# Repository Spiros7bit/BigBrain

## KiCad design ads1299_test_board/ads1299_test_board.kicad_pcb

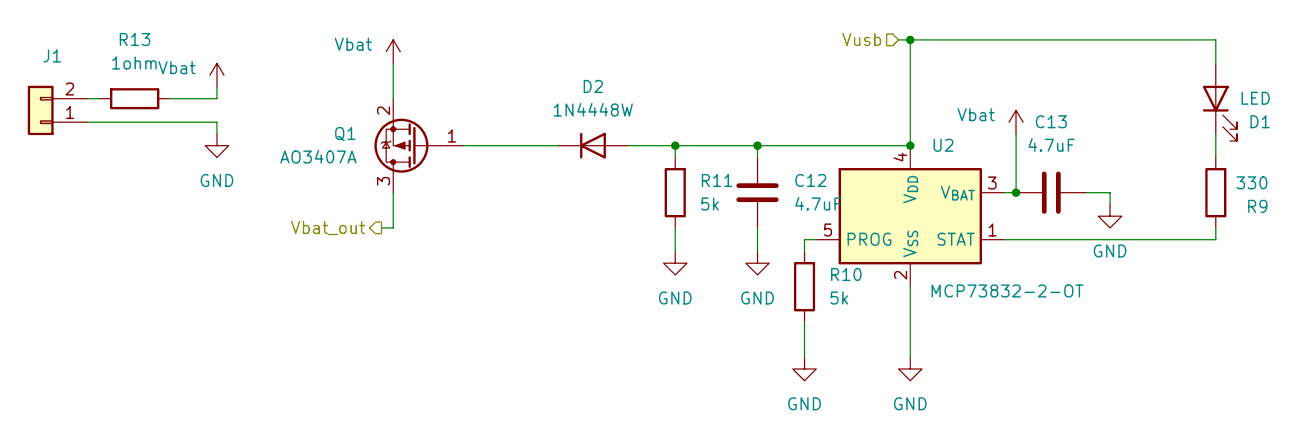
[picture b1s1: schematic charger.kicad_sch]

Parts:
C12, C13: 4.7uF; C_0402_1005Metric_Pad0.74x0.62mm_HandSolder
D1: LED; LED_0603_1608Metric
D2: 1N4448W; D_SOD-123
J1: Conn_01x02; JST_EH_B2B-EH-A_1x02_P2.50mm_Vertical
Q1: AO3407A; SOT-23
R9: 330; R_0402_1005Metric_Pad0.72x0.64mm_HandSolder
R10, R11: 5k; R_0402_1005Metric_Pad0.72x0.64mm_HandSolder
R13: 1ohm; TO-252-2_TabPin1
U2: MCP73832-2-OT; SOT-23-5

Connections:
/USB/Vbus: C12.1, D1.2 (A), D2.2 (A), Q1.3 (D), R11.2, U2.4 (V_{DD}); also elsewhere on the board
GND: C12.2, C13.2, J1.1, R10.1, R11.1, U2.2 (V_{SS}); also elsewhere on the board
unnamed: D1.1 (K), R9.2
unnamed: D2.1 (K), Q1.1 (G)
unnamed: J1.2, R13.2
unnamed: R10.2, U2.5 (PROG)
unnamed: R9.1, U2.1 (STAT)
Vbat: C13.1, Q1.2 (S), R13.1, U2.3 (V_{BAT})

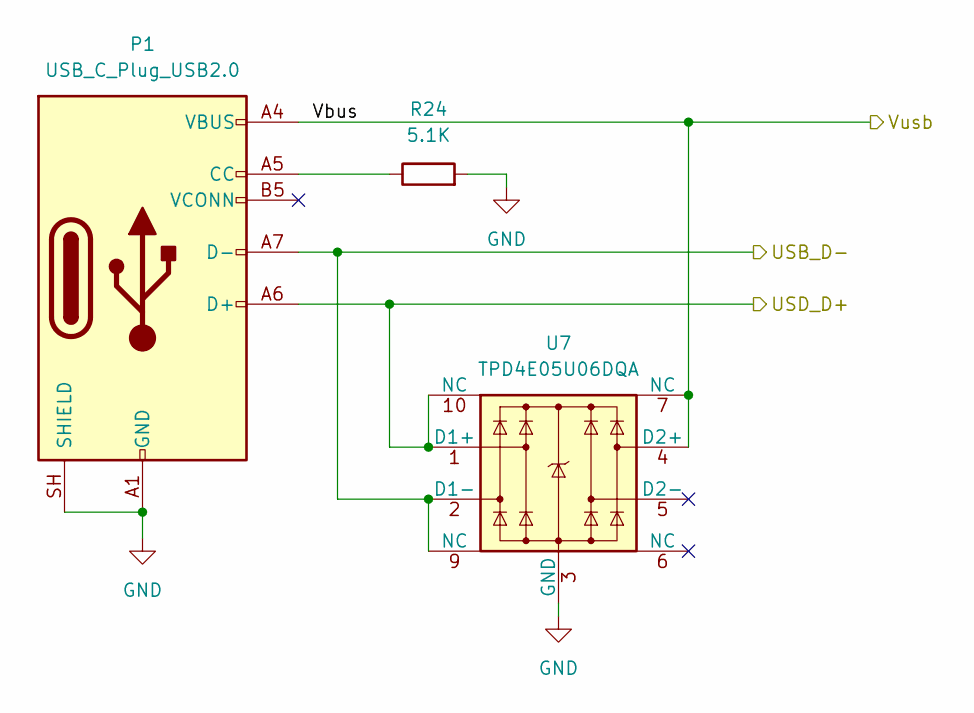
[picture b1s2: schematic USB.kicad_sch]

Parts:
P1: USB_C_Plug_USB2.0; USB_C_Receptacle_G-Switch_GT-USB-7010ASV
R24: 5.1K; C_0402_1005Metric_Pad0.74x0.62mm_HandSolder
U7: TPD4E05U06DQA; USON-10_2.5x1.0mm_P0.5mm

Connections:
/ESP32_S3_WROOM/USB_D+: P1.A6 (D+), U7.1 (D1+), U7.10 (NC); also elsewhere on the board
/ESP32_S3_WROOM/USB_D-: P1.A7 (D-), U7.2 (D1-), U7.9 (NC); also elsewhere on the board
/USB/Vbus: P1.A4 (VBUS), P1.A9 (VBUS), P1.B4 (VBUS), P1.B9 (VBUS), U7.4 (D2+), U7.7 (NC); also elsewhere on the board
GND: P1.A1 (GND), P1.A12 (GND), P1.B1 (GND), P1.B12 (GND), P1.SH (SHIELD), R24.2, U7.3 (GND), U7.8 (GND); also elsewhere on the board
unnamed: P1.A5 (CC), R24.1

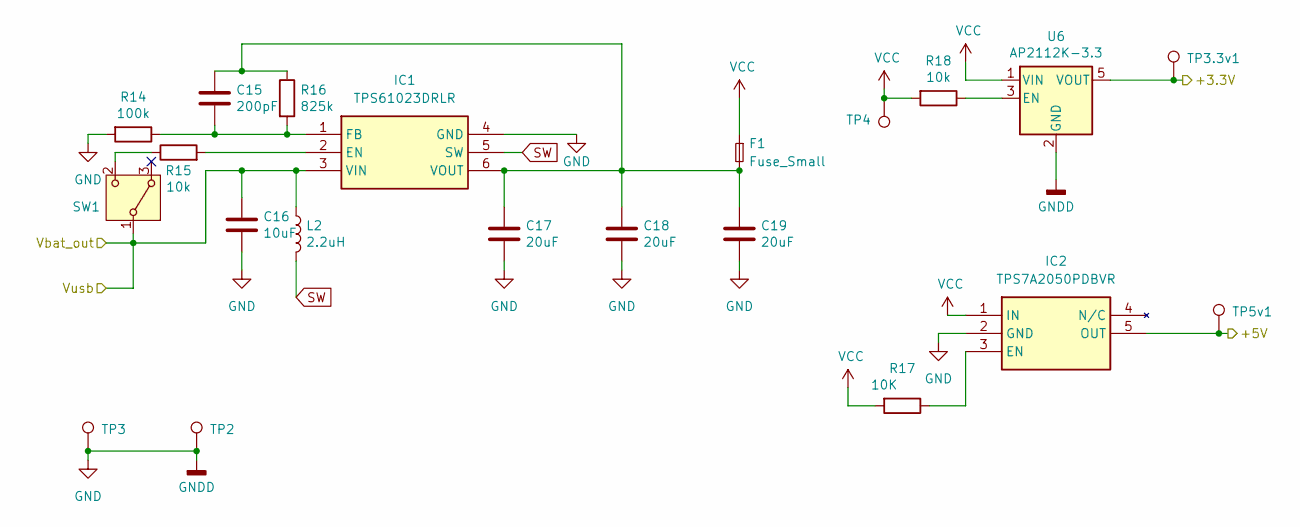
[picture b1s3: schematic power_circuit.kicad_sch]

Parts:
C15: 200pF; C_0402_1005Metric_Pad0.74x0.62mm_HandSolder
C16: 10uF; C_0402_1005Metric_Pad0.74x0.62mm_HandSolder
C17, C18, C19: 20uF; C_0805_2012Metric_Pad1.18x1.45mm_HandSolder
F1: Fuse_Small; Fuse_2512_6332Metric_Pad1.52x3.35mm_HandSolder
IC1: TPS61023DRLR; SOT-563; Manufacturer_Part_Number TPS61023DRLR; Mouser Part Number 595-TPS61023DRLR
IC2: TPS7A2050PDBVR; SOT-23-5_HandSoldering; Manufacturer_Part_Number TPS7A2050PDBVR; Mouser Part Number 595-TPS7A2050PDBVR
L2: 2.2uH; L_Wuerth_HCI-5040
R14: 100k; R_0402_1005Metric_Pad0.72x0.64mm_HandSolder
R15, R18: 10k; R_0402_1005Metric_Pad0.72x0.64mm_HandSolder
R16: 825k; R_0402_1005Metric_Pad0.72x0.64mm_HandSolder
R17: 10K; R_0402_1005Metric_Pad0.72x0.64mm_HandSolder
SW1: EG1218; SW_Slide-03_Wuerth-WS-SLTV_10x2.5x6.4_P2.54mm
TP2, TP3, TP3.3v1, TP4, TP5v1: TestPoint; TestPoint_Pad_D1.0mm
U6: AP2112K-3.3; SOT-23-5

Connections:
/USB/Vbus: C16.1, IC1.3 (VIN), L2.1, SW1.1 (B); also elsewhere on the board
/ads1299_AFE_/AVDD: IC2.5 (OUT), TP5v1.1 (1_1); also elsewhere on the board
/ads1299_AFE_/DVDD: TP3.3v1.1 (1_1), U6.5 (VOUT); also elsewhere on the board
GND: C16.2, C17.2, C18.2, C19.2, IC1.4 (GND), IC2.2 (GND), R14.2, TP2.1 (1_1), TP3.1 (1_1), U6.2 (GND); also elsewhere on the board
unnamed: IC1.2 (EN), R15.2
unnamed: C15.2, IC1.1 (FB), R14.1, R16.2
unnamed: C15.1, C17.1, C18.1, C19.1, F1.2, IC1.6 (VOUT), R16.1
unnamed: IC2.3 (EN), R17.1
unnamed: R15.1, SW1.2 (C)
unnamed: R18.1, U6.3 (EN)
SW: IC1.5 (SW), L2.2
VCC: F1.1, IC2.1 (IN), R17.2, R18.2, TP4.1 (1_1), U6.1 (VIN)

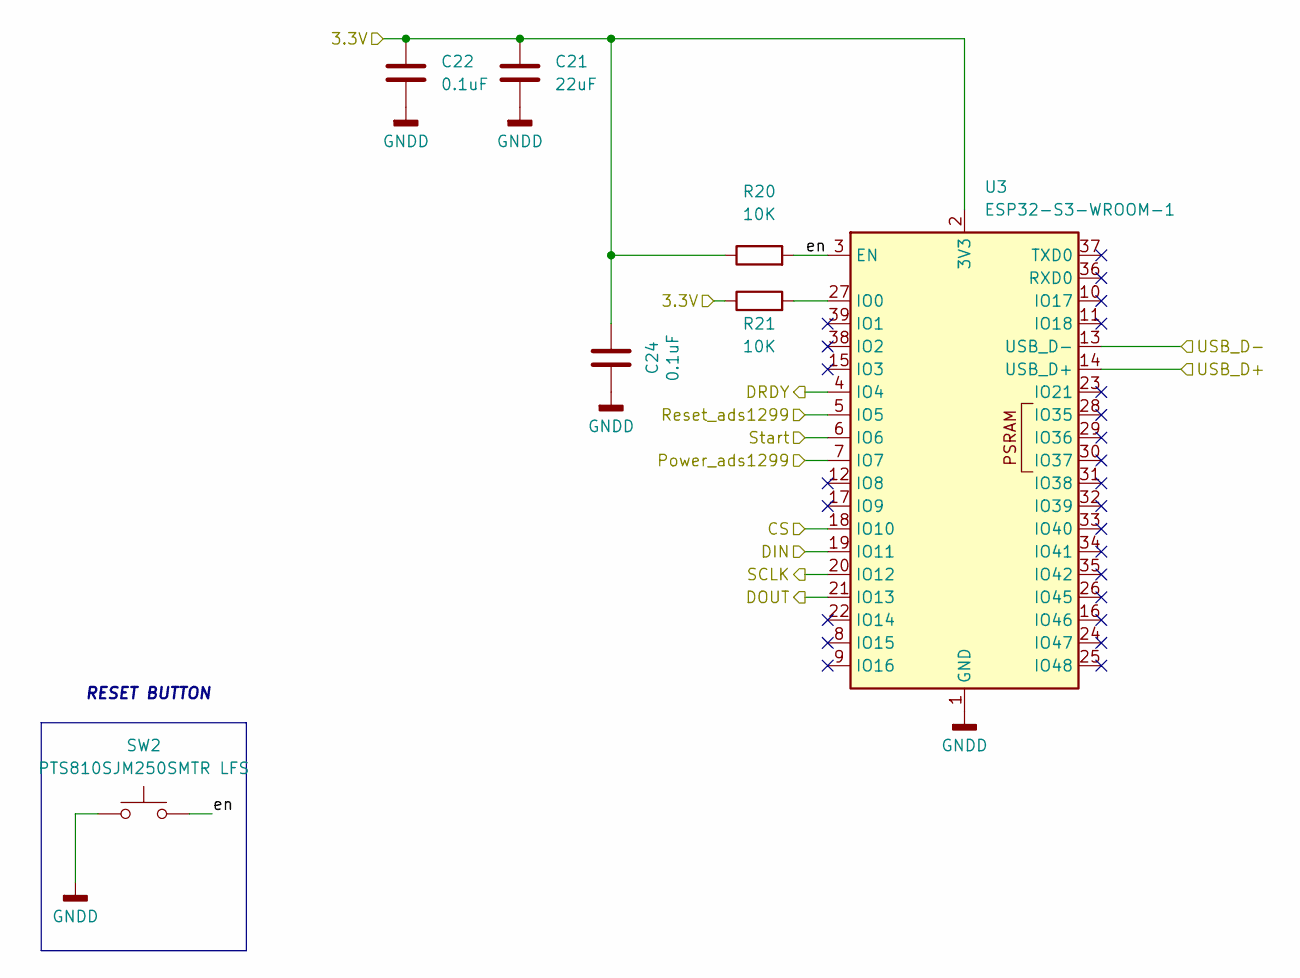
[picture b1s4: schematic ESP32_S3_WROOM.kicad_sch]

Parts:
C21: 22uF; C_0603_1608Metric_Pad1.08x0.95mm_HandSolder
C22, C24: 0.1uF; C_0402_1005Metric_Pad0.74x0.62mm_HandSolder
R20, R21: 10K; R_0402_1005Metric_Pad0.72x0.64mm_HandSolder
SW2: PTS810SJM250SMTR LFS; SW_SPST_PTS810
U3: ESP32-S3-WROOM-1

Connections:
/ESP32_S3_WROOM/CS: U3.18 (IO10); also elsewhere on the board
/ESP32_S3_WROOM/DIN: U3.19 (IO11); also elsewhere on the board
/ESP32_S3_WROOM/DOUT: U3.21 (IO13); also elsewhere on the board
/ESP32_S3_WROOM/DRDY: U3.4 (IO4); also elsewhere on the board
/ESP32_S3_WROOM/Power_ads1299: U3.7 (IO7); also elsewhere on the board
/ESP32_S3_WROOM/Reset_ads1299: U3.5 (IO5); also elsewhere on the board
/ESP32_S3_WROOM/SCLK: U3.20 (IO12); also elsewhere on the board
/ESP32_S3_WROOM/Start: U3.6 (IO6); also elsewhere on the board
/ESP32_S3_WROOM/USB_D+: U3.14 (USB_D+); also elsewhere on the board
/ESP32_S3_WROOM/USB_D-: U3.13 (USB_D-); also elsewhere on the board
/ESP32_S3_WROOM/en: R20.2, SW2.2, U3.3 (EN)
/ads1299_AFE_/DVDD: C21.1, C22.1, C24.1, R20.1, R21.1, U3.2 (3V3); also elsewhere on the board
GND: C21.2, C22.2, C24.2, SW2.1, U3.1 (GND), U3.40 (GND), U3.41 (GND); also elsewhere on the board
unnamed: R21.2, U3.27 (IO0)

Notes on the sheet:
RESET BUTTON

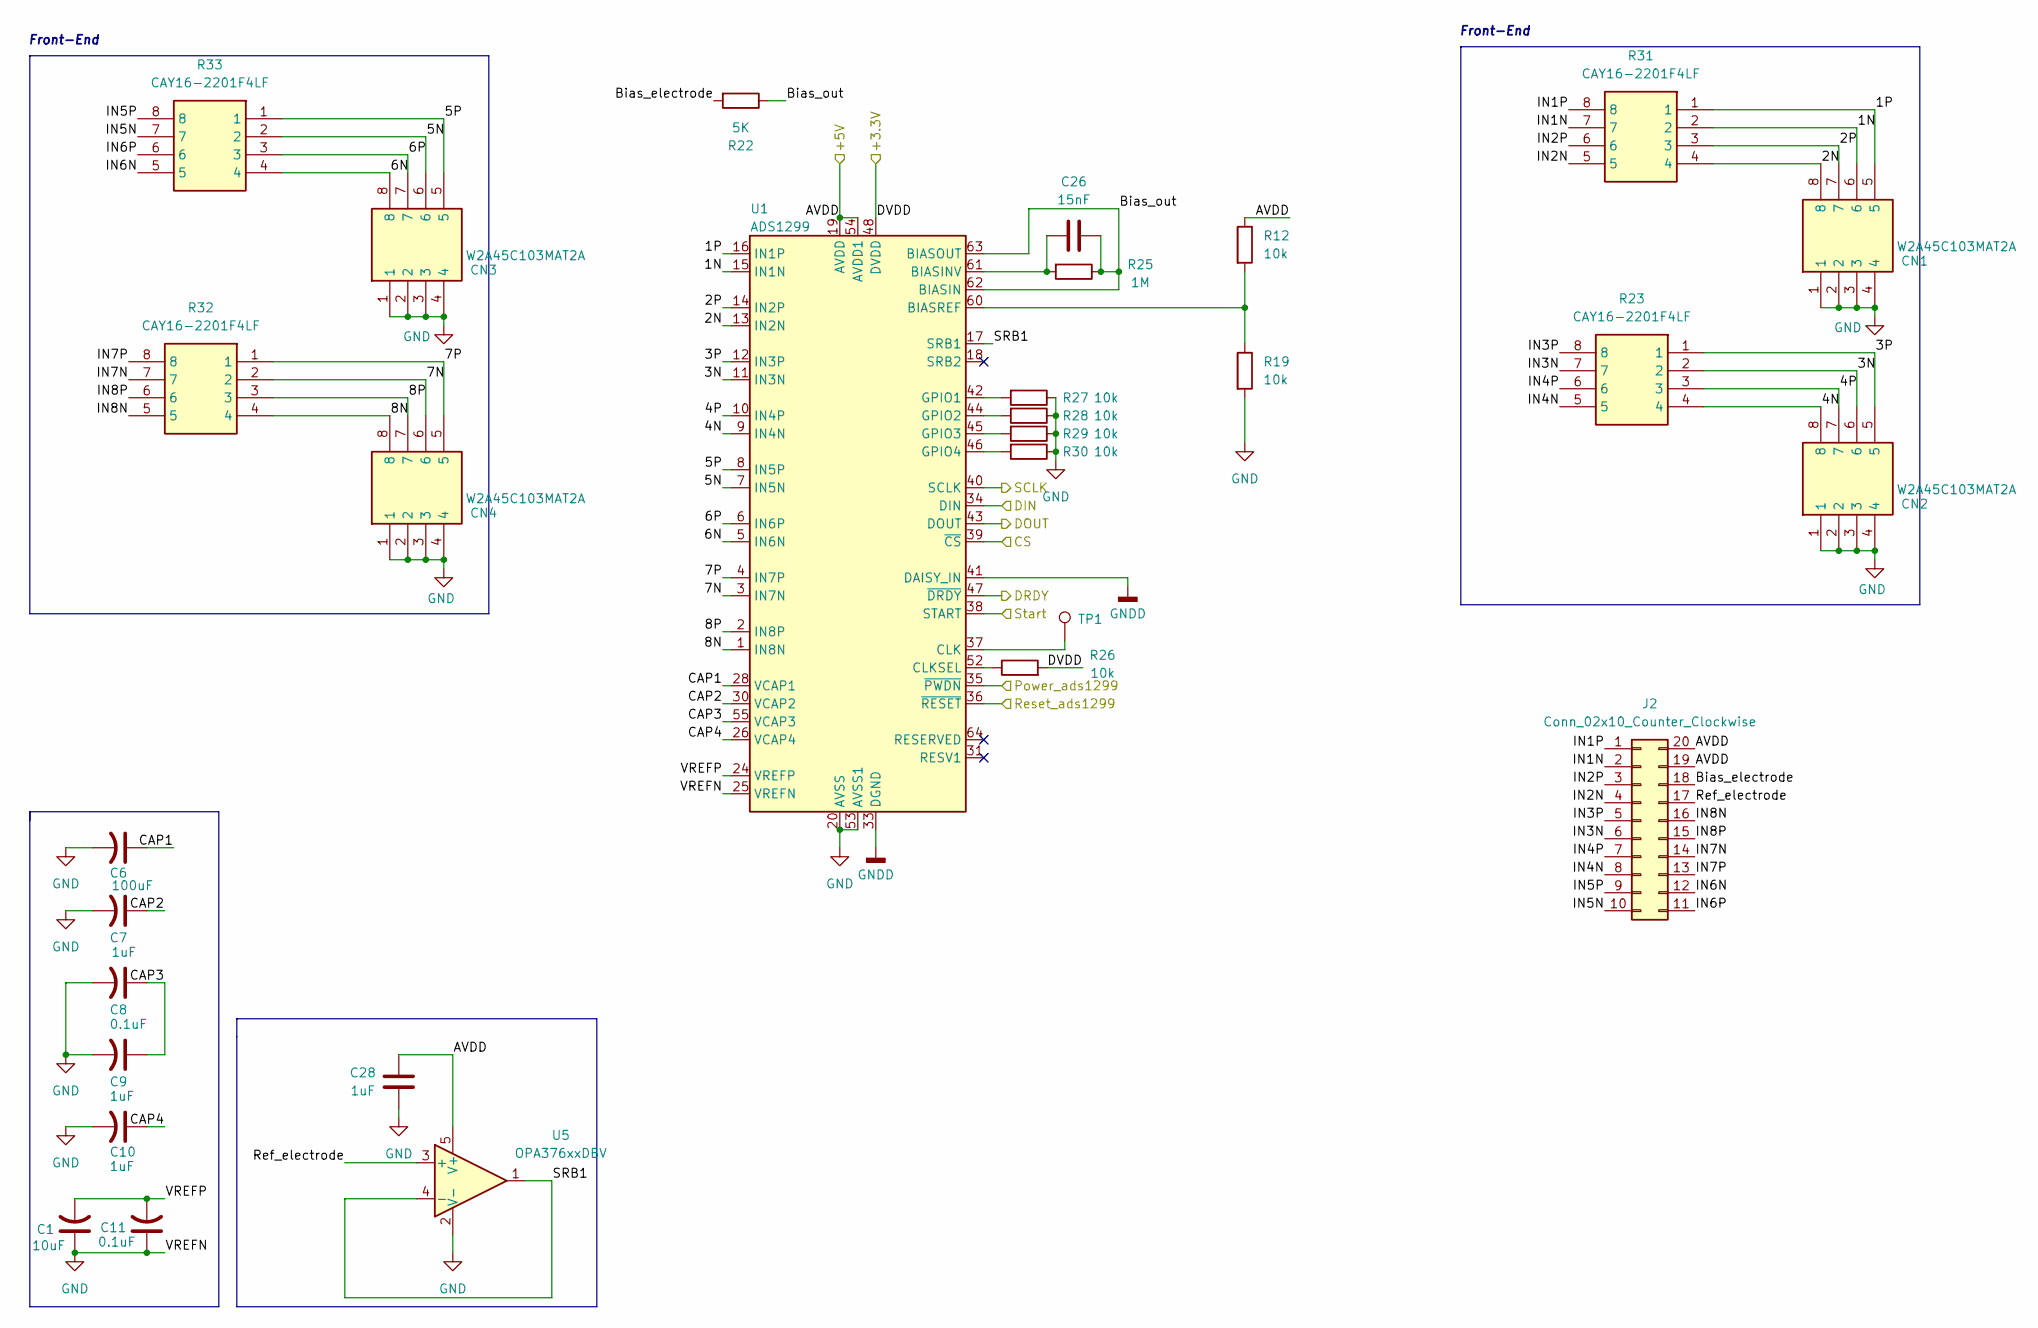
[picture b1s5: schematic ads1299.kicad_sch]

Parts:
C1: 10uF; C_0402_1005Metric_Pad0.74x0.62mm_HandSolder
C6: 100uF; C_1206_3216Metric_Pad1.33x1.80mm_HandSolder
C7, C9, C10, C28: 1uF; C_0402_1005Metric_Pad0.74x0.62mm_HandSolder
C8, C11: 0.1uF; C_0402_1005Metric_Pad0.74x0.62mm_HandSolder
C26: 15nF; C_0402_1005Metric_Pad0.74x0.62mm_HandSolder
CN1, CN2, CN3, CN4: W2A45C103MAT2A; Manufacturer_Part_Number W2A45C103MAT2A; Mouser Part Number 581-W2A45C103MAT2A
J2: Conn_02x10_Counter_Clockwise; IDC-Header_2x10_P2.54mm_Vertical
R12, R19, R26, R27, R28, R29, R30: 10k; R_0402_1005Metric_Pad0.72x0.64mm_HandSolder
R22: 5K; C_0402_1005Metric_Pad0.74x0.62mm_HandSolder
R23, R31, R32, R33: CAY16-2201F4LF; RESCAX80P160X320X60-8N; Manufacturer_Part_Number CAY16-2201F4LF; Mouser Part Number 652-CAY16-2201F4LF
R25: 1M; R_0402_1005Metric_Pad0.72x0.64mm_HandSolder
TP1: TestPoint; TestPoint_Pad_D1.0mm
U1: ADS1299; TQFP-64_10x10mm_P0.5mm
U5: OPA376xxDBV; SOT-23-5

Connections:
/ESP32_S3_WROOM/CS: U1.39 (~CS); also elsewhere on the board
/ESP32_S3_WROOM/DIN: U1.34 (DIN); also elsewhere on the board
/ESP32_S3_WROOM/DOUT: U1.43 (DOUT); also elsewhere on the board
/ESP32_S3_WROOM/DRDY: U1.47 (~DRDY); also elsewhere on the board
/ESP32_S3_WROOM/Power_ads1299: U1.35 (~PWDN); also elsewhere on the board
/ESP32_S3_WROOM/Reset_ads1299: U1.36 (~RESET); also elsewhere on the board
/ESP32_S3_WROOM/SCLK: U1.40 (SCLK); also elsewhere on the board
/ESP32_S3_WROOM/Start: U1.38 (START); also elsewhere on the board
/ads1299_AFE_/1N: CN1.6, R31.2, U1.15 (IN1N)
/ads1299_AFE_/1P: CN1.5, R31.1, U1.16 (IN1P)
/ads1299_AFE_/2N: CN1.8, R31.4, U1.13 (IN2N)
/ads1299_AFE_/2P: CN1.7, R31.3, U1.14 (IN2P)
/ads1299_AFE_/3N: CN2.6, R23.2, U1.11 (IN3N)
/ads1299_AFE_/3P: CN2.5, R23.1, U1.12 (IN3P)
/ads1299_AFE_/4N: CN2.8, R23.4, U1.9 (IN4N)
/ads1299_AFE_/4P: CN2.7, R23.3, U1.10 (IN4P)
/ads1299_AFE_/5N: CN3.6, R33.2, U1.7 (IN5N)
/ads1299_AFE_/5P: CN3.5, R33.1, U1.8 (IN5P)
/ads1299_AFE_/6N: CN3.8, R33.4, U1.5 (IN6N)
/ads1299_AFE_/6P: CN3.7, R33.3, U1.6 (IN6P)
/ads1299_AFE_/7N: CN4.6, R32.2, U1.3 (IN7N)
/ads1299_AFE_/7P: CN4.5, R32.1, U1.4 (IN7P)
/ads1299_AFE_/8N: CN4.8, R32.4, U1.1 (IN8N)
/ads1299_AFE_/8P: CN4.7, R32.3, U1.2 (IN8P)
/ads1299_AFE_/AVDD: C28.1, J2.19, J2.20, R12.1, U1.19 (AVDD), U1.21 (AVDD), U1.22 (AVDD), U1.54 (AVDD1), U1.56 (AVDD), U1.59 (AVDD), U5.5 (V+); also elsewhere on the board
/ads1299_AFE_/Bias_electrode: J2.18, R22.2
/ads1299_AFE_/Bias_out: C26.2, R22.1, R25.1, U1.62 (BIASIN), U1.63 (BIASOUT)
/ads1299_AFE_/CAP1: C6.1, U1.28 (VCAP1)
/ads1299_AFE_/CAP2: C7.1, U1.30 (VCAP2)
/ads1299_AFE_/CAP3: C8.1, C9.1, U1.55 (VCAP3)
/ads1299_AFE_/CAP4: C10.1, U1.26 (VCAP4)
/ads1299_AFE_/DVDD: R26.2, U1.48 (DVDD), U1.50 (DVDD); also elsewhere on the board
/ads1299_AFE_/IN1N: J2.2, R31.7
/ads1299_AFE_/IN1P: J2.1, R31.8
/ads1299_AFE_/IN2N: J2.4, R31.5
/ads1299_AFE_/IN2P: J2.3, R31.6
/ads1299_AFE_/IN3N: J2.6, R23.7
/ads1299_AFE_/IN3P: J2.5, R23.8
/ads1299_AFE_/IN4N: J2.8, R23.5
/ads1299_AFE_/IN4P: J2.7, R23.6
/ads1299_AFE_/IN5N: J2.10, R33.7
/ads1299_AFE_/IN5P: J2.9, R33.8
/ads1299_AFE_/IN6N: J2.12, R33.5
/ads1299_AFE_/IN6P: J2.11, R33.6
/ads1299_AFE_/IN7N: J2.14, R32.7
/ads1299_AFE_/IN7P: J2.13, R32.8
/ads1299_AFE_/IN8N: J2.16, R32.5
/ads1299_AFE_/IN8P: J2.15, R32.6
/ads1299_AFE_/Ref_electrode: J2.17, U5.3 (+)
/ads1299_AFE_/SRB1: U1.17 (SRB1), U5.1, U5.4 (-)
/ads1299_AFE_/VREFP: C1.2, C11.2, U1.24 (VREFP)
GND: C1.1, C6.2, C7.2, C8.2, C9.2, C10.2, C11.1, C28.2, CN1.1, CN1.2, CN1.3, CN1.4, CN2.1, CN2.2, CN2.3, CN2.4, CN3.1, CN3.2, CN3.3, CN3.4, CN4.1, CN4.2, CN4.3, CN4.4, R19.2, R27.1, R28.1, R29.1, R30.1, U1.20 (AVSS), U1.23 (AVSS), U1.25 (VREFN), U1.32 (AVSS), U1.33 (DGND), U1.41 (DAISY_IN), U1.49 (DGND), U1.51 (DGND), U1.53 (AVSS1), U1.57 (AVSS), U1.58 (AVSS), U5.2 (V-); also elsewhere on the board
unnamed: C26.1, R25.2, U1.61 (BIASINV)
unnamed: R12.2, R19.1, U1.60 (BIASREF)
unnamed: TP1.1 (1_1), U1.37 (CLK)
unnamed: R26.1, U1.52 (CLKSEL)
unnamed: R27.2, U1.42 (GPIO1)
unnamed: R28.2, U1.44 (GPIO2)
unnamed: R29.2, U1.45 (GPIO3)
unnamed: R30.2, U1.46 (GPIO4)

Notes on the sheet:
Front-End

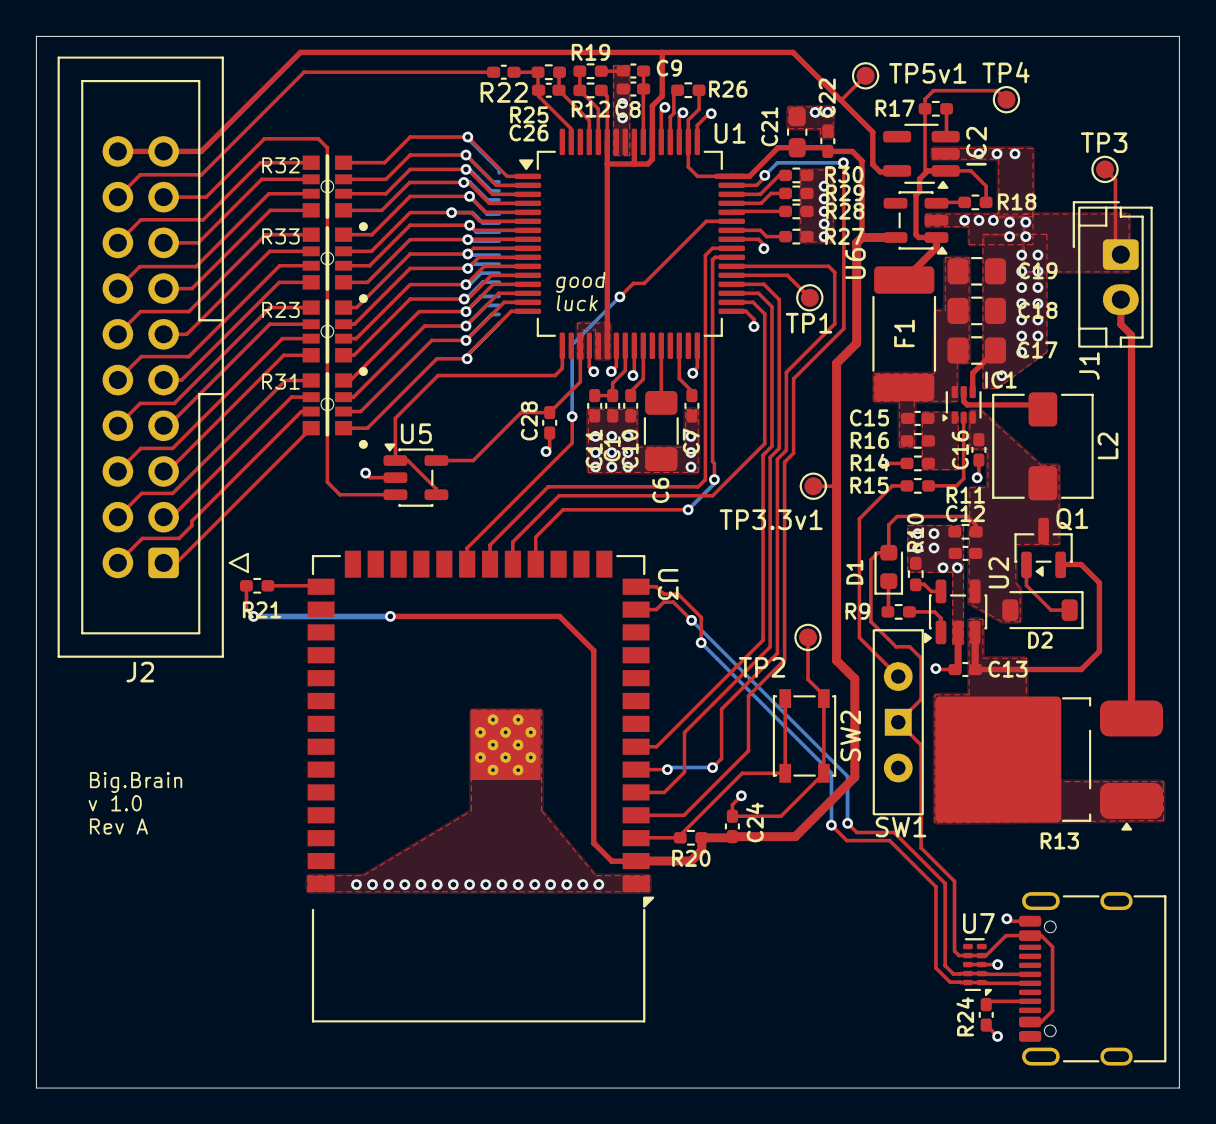
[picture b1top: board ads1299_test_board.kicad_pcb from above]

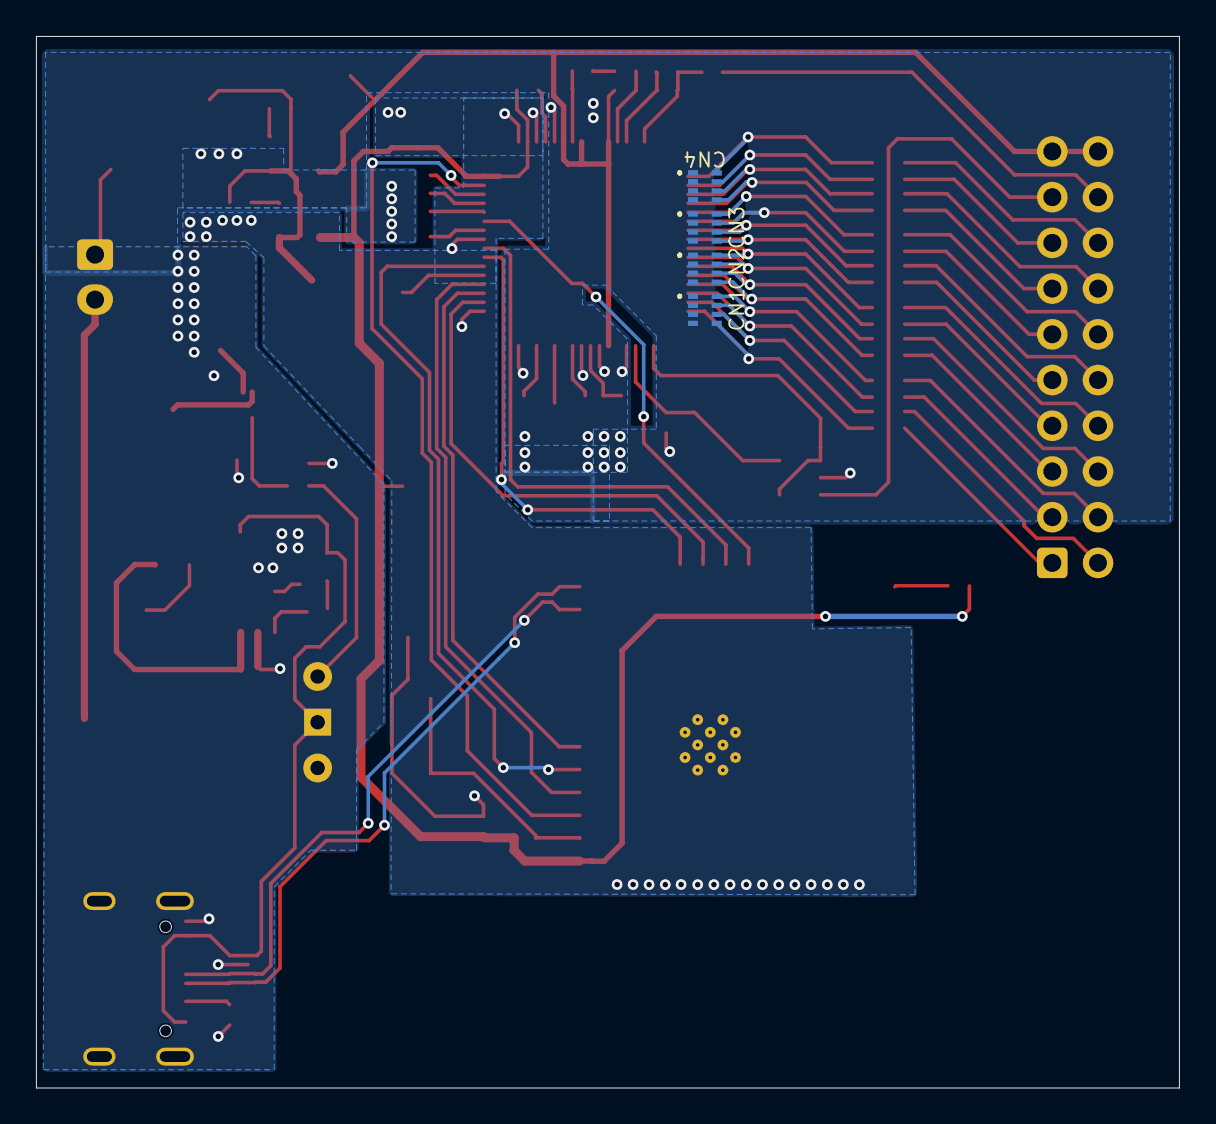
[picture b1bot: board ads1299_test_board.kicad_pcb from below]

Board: 2 copper layers, 63.5 x 58.4 mm, 72 parts (4 on the bottom side), 80 nets.

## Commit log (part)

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2026-05-12 Add files via upload
    KiCad files
2026-05-12 Datasheet with notes
2026-05-22 new notes
2026-05-22 Changed the schematic architecture and made the charger schematic
2026-05-23 Add files via upload
    ADS1299 evaluation board from TI
2026-05-25 power circuit
2026-05-27 Create power_management file
    This file contains the schematic for Boost converter and LDOs
2026-05-27 3 files of kicad
    These files are the schematic of Boost Converter and LDOs
2026-05-27 add libraries with symbols, footprints and 3d
2026-05-27 Added spiro's schematic to project. Also added lib folder
2026-05-27 27/05
2026-05-28 Add files via upload
    footprint of TPS7A20 andTPS1023
2026-05-28 Add files via upload
    Add schematic symbols of TPS61023 and TPS7A20
2026-05-28 lib update
2026-05-28 charger circuit
2026-05-30 usb, esp32 s3 wroom 1
2026-06-02 usb charge and power circuit switch
2026-06-04 work on ads1299 schematic
2026-06-06 GPIO, SRB
2026-06-15 fixed Vbat net name
